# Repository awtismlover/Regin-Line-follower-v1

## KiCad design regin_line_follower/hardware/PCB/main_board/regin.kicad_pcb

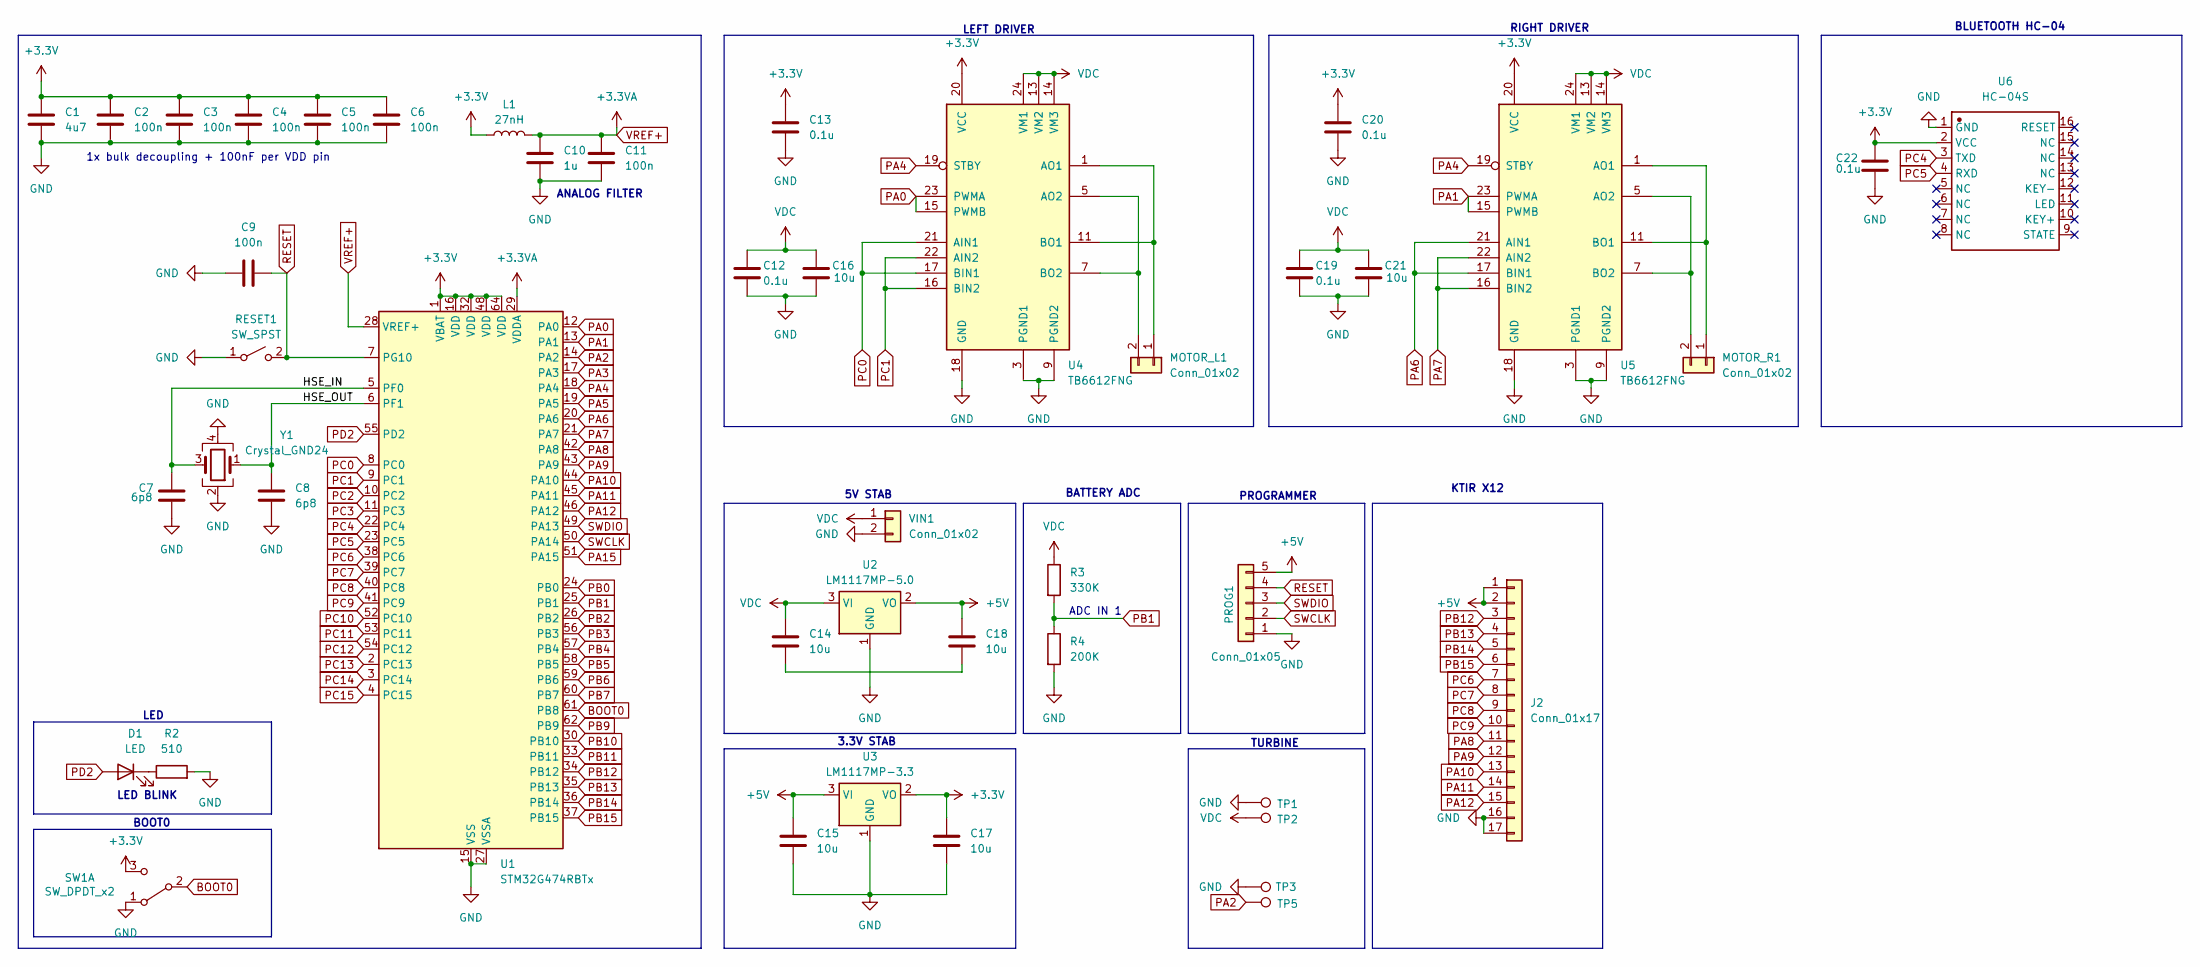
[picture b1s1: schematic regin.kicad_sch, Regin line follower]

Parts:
C1: 4u7; C_0603_1608Metric
C2, C3, C4, C5, C6, C9, C11: 100n; C_0603_1608Metric
C7, C8: 6p8; C_0603_1608Metric
C10: 1u; C_0603_1608Metric
C12, C13, C19, C20, C22: 0.1u; C_0603_1608Metric
C14, C15, C16, C17, C18, C21: 10u; C_0603_1608Metric
D1: LED; LED_0603_1608Metric
J2: Conn_01x17; Hirose_FH12-17S-0.5SH_1x17-1MP_P0.50mm_Horizontal
L1: 27nH; L_0603_1608Metric
MOTOR_L1: Conn_01x02; PinHeader_1x02_P2.54mm_Vertical
MOTOR_R1: Conn_01x02; PinHeader_1x02_P2.54mm_Vertical
PROG1: Conn_01x05; PinHeader_1x05_P2.54mm_Vertical
R2: 510; C_0603_1608Metric
R3: 330K; C_0603_1608Metric
R4: 200K; C_0603_1608Metric
RESET1: SW_SPST; SW_SPST_CK_RS282G05A3
SW1: SW_DPDT_x2; SW_SPDT_PCM12
TP1, TP2: TestPoint; TestPoint_Pad_D2.5mm
TP3, TP5: TestPoint; TestPoint_Pad_D1.0mm
U1: STM32G474RBTx; LQFP-64_10x10mm_P0.5mm
U2: LM1117MP-5.0; SOT-223-3_TabPin2
U3: LM1117MP-3.3; SOT-223-3_TabPin2
U4, U5: TB6612FNG; SSOP-24_5.3x8.2mm_P0.65mm
U6: HC-04S; hc-04; Manufacturer Part HC-04S
VIN1: Conn_01x02; PinSocket_1x02_P2.54mm_Vertical
Y1: Crystal_GND24; Crystal_SMD_2016-4Pin_2.0x1.6mm

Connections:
+3.3V: C1.1, C2.1, C3.1, C4.1, C5.1, C6.1, C13.1, C17.1, C20.1, C22.2, L1.1, SW1.3 (C), U1.1 (VBAT), U1.16 (VDD), U1.32 (VDD), U1.48 (VDD), U1.64 (VDD), U3.2 (VO), U4.20 (VCC), U5.20 (VCC), U6.2 (VCC)
+5V: C15.1, C18.1, J2.1, J2.2, PROG1.5, U2.2 (VO), U3.3 (VI)
/HSE_IN: C7.1, U1.5 (PF0), Y1.3
/HSE_OUT: C8.1, U1.6 (PF1), Y1.1
BOOT0: SW1.2 (B), U1.61 (PB8)
GND: C1.2, C2.2, C3.2, C4.2, C5.2, C6.2, C7.2, C8.2, C9.1, C10.2, C11.2, C12.2, C13.2, C15.2, C16.2, C17.2, C19.2, C20.2, C21.2, C22.1, J2.16, J2.17, PROG1.1, R2.2, R4.2, RESET1.1 (A), SW1.1 (A), TP1.1, TP3.1, U1.15 (VSS), U1.27 (VSSA), U1.31 (VSS), U1.47 (VSS), U1.63 (VSS), U2.1 (GND), U3.1 (GND), U4.3 (PGND1), U4.4 (PGND1), U4.9 (PGND2), U4.10 (PGND2), U4.18 (GND), U5.3 (PGND1), U5.4 (PGND1), U5.9 (PGND2), U5.10 (PGND2), U5.18 (GND), U6.1 (GND), VIN1.2, Y1.2, Y1.4; also elsewhere on the board
unnamed: C14.2, C18.2
unnamed: D1.1 (K), R2.1
unnamed: MOTOR_L1.1, U4.1 (AO1), U4.2 (AO1), U4.11 (BO1), U4.12 (BO1)
unnamed: MOTOR_L1.2, U4.5 (AO2), U4.6 (AO2), U4.7 (BO2), U4.8 (BO2)
unnamed: MOTOR_R1.1, U5.1 (AO1), U5.2 (AO1), U5.11 (BO1), U5.12 (BO1)
unnamed: MOTOR_R1.2, U5.5 (AO2), U5.6 (AO2), U5.7 (BO2), U5.8 (BO2)
PA0: U1.12 (PA0), U4.15 (PWMB), U4.23 (PWMA)
PA1: U1.13 (PA1), U5.15 (PWMB), U5.23 (PWMA)
PA2: TP5.1, U1.14 (PA2); also elsewhere on the board
PA3: U1.17 (PA3)
PA4: U1.18 (PA4), U4.19 (STBY), U5.19 (STBY)
PA5: U1.19 (PA5)
PA6: U1.20 (PA6), U5.17 (BIN1), U5.21 (AIN1)
PA7: U1.21 (PA7), U5.16 (BIN2), U5.22 (AIN2)
PA8: J2.11, U1.42 (PA8)
PA9: J2.12, U1.43 (PA9)
PA10: J2.13, U1.44 (PA10)
PA11: J2.14, U1.45 (PA11)
PA12: J2.15, U1.46 (PA12)
PA15: U1.51 (PA15)
PB0: U1.24 (PB0)
PB1: R3.2, R4.1, U1.25 (PB1)
PB2: U1.26 (PB2)
PB3: U1.56 (PB3)
PB4: U1.57 (PB4)
PB5: U1.58 (PB5)
PB6: U1.59 (PB6)
PB7: U1.60 (PB7)
PB9: U1.62 (PB9)
PB10: U1.30 (PB10)
PB11: U1.33 (PB11)
PB12: J2.3, U1.34 (PB12)
PB13: J2.4, U1.35 (PB13)
PB14: J2.5, U1.36 (PB14)
PB15: J2.6, U1.37 (PB15)
PC0: U1.8 (PC0), U4.17 (BIN1), U4.21 (AIN1)
PC1: U1.9 (PC1), U4.16 (BIN2), U4.22 (AIN2)
PC2: U1.10 (PC2)
PC3: U1.11 (PC3)
PC4: U1.22 (PC4), U6.3 (TXD)
PC5: U1.23 (PC5), U6.4 (RXD)
PC6: J2.7, U1.38 (PC6)
PC7: J2.8, U1.39 (PC7)
PC8: J2.9, U1.40 (PC8)
PC9: J2.10, U1.41 (PC9)
PC10: U1.52 (PC10)
PC11: U1.53 (PC11)
PC12: U1.54 (PC12)
PC13: U1.2 (PC13)
PC14: U1.3 (PC14)
PC15: U1.4 (PC15)
PD2: D1.2 (A), U1.55 (PD2)
RESET: C9.2, PROG1.4, RESET1.2 (B), U1.7 (PG10)
SWCLK: PROG1.2, U1.50 (PA14)
SWDIO: PROG1.3, U1.49 (PA13)
VDC: C12.1, C14.1, C16.1, C19.1, C21.1, R3.1, TP2.1, U2.3 (VI), U4.13 (VM2), U4.14 (VM3), U4.24 (VM1), U5.13 (VM2), U5.14 (VM3), U5.24 (VM1), VIN1.1; also elsewhere on the board
VREF+: C10.1, C11.1, L1.2, U1.28 (VREF+), U1.29 (VDDA)

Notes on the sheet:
ADC IN 1
ANALOG FILTER
TURBINE
1x bulk decoupling + 100nF per VDD pin
RIGHT DRIVER
3.3V STAB
LED
BATTERY ADC
5V STAB
BLUETOOTH HC-04
PROGRAMMER
KTIR X12
BOOT0
LEFT DRIVER
LED BLINK

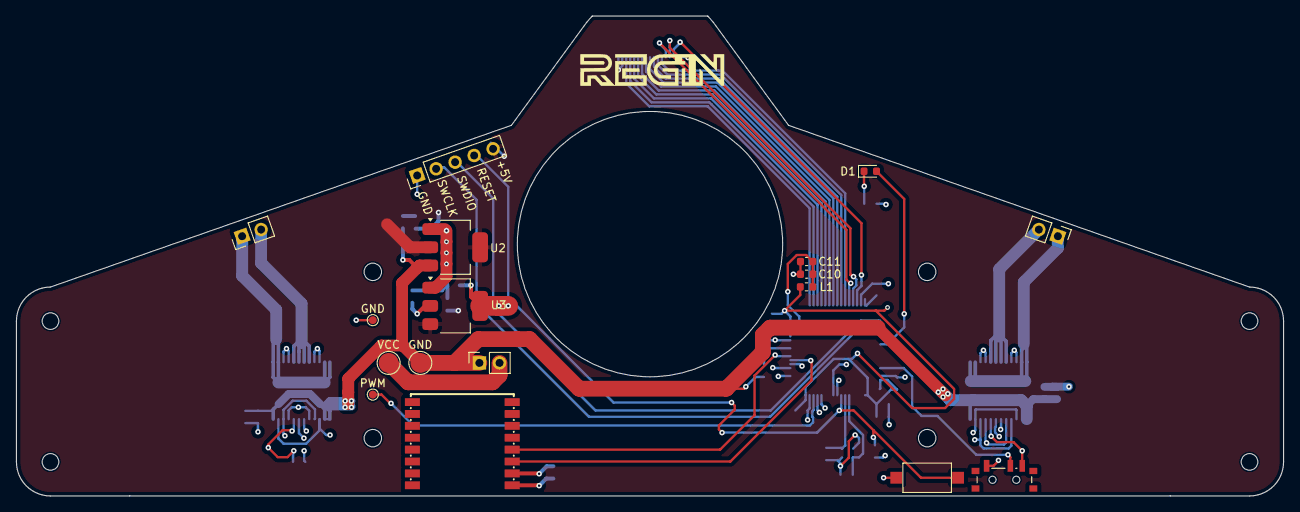
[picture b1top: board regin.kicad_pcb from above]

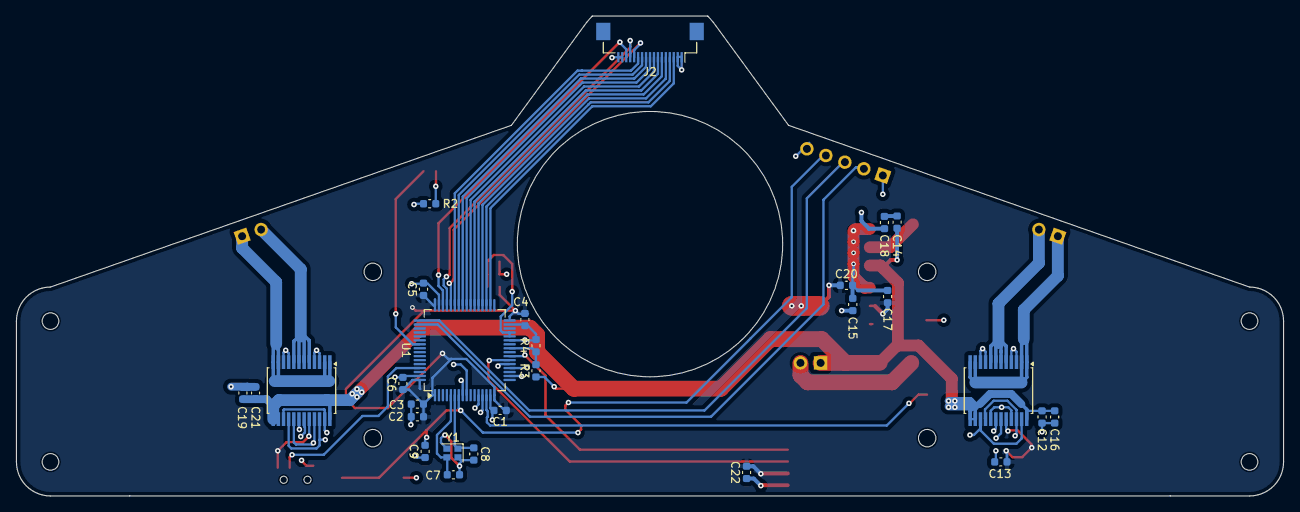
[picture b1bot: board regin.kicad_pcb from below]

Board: 4 copper layers, 160.0 x 60.6 mm, 49 parts (28 on the bottom side), 42 nets.

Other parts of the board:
GND: TestPoint; TestPoint_Pad_D2.5mm
GND#2: TestPoint; TestPoint_Pad_D1.0mm
H1, H2, H3, H4: MountingHole; MountingHole_2.2mm_M2
PWM: TestPoint; TestPoint_Pad_D1.0mm
VCC: TestPoint; TestPoint_Pad_D2.5mm

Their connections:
GND: GND#2.1, VCC.1; also elsewhere on the board
PA2: PWM.1; also elsewhere on the board
VDC: GND.1; also elsewhere on the board

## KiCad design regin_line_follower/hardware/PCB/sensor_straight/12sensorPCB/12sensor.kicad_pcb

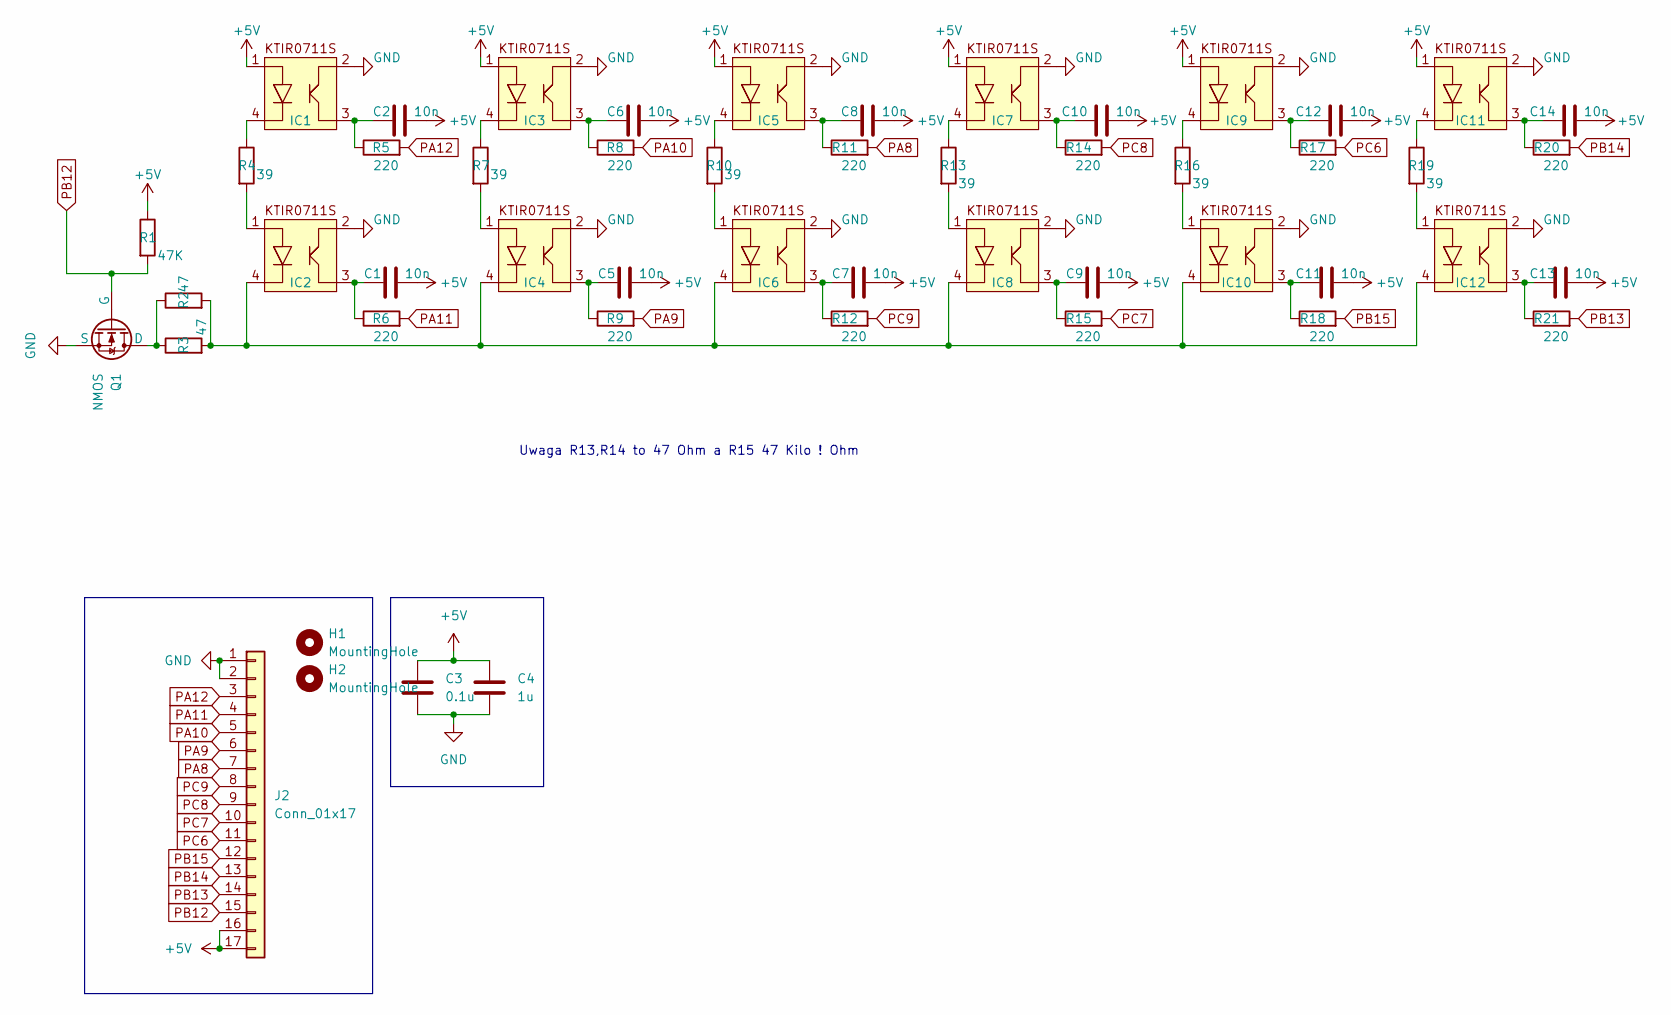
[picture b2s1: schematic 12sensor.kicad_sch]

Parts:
C1, C2, C5, C6, C7, C8, C9, C10, C11, C12, C13, C14: 10n; C_0603_1608Metric
C3: 0.1u; C_0603_1608Metric
C4: 1u; C_0603_1608Metric
H1, H2: MountingHole; MountingHole_2.2mm_M2
IC1, IC2, IC3, IC4, IC5, IC6, IC7, IC8, IC9, IC10, IC11, IC12: KTIR0711S
J2: Conn_01x17; Hirose_FH12-17S-0.5SH_1x17-1MP_P0.50mm_Horizontal
Q1: NMOS; NMOS_SN
R1: 47K; R_0603_1608Metric
R2, R3: 47; R_0603_1608Metric
R4, R7, R10, R13, R16, R19: 39; R_0603_1608Metric
R5, R6, R8, R9, R11, R12, R14, R15, R17, R18, R20, R21: 220; R_0603_1608Metric

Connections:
+5V: C1.2, C2.2, C3.1, C4.1, C5.2, C6.2, C7.2, C8.2, C9.2, C10.2, C11.2, C12.2, C13.2, C14.2, IC1.1, IC3.1, IC5.1, IC7.1, IC9.1, IC11.1, J2.16, J2.17, R1.1; also elsewhere on the board
GND: C3.2, C4.2, IC1.2, IC2.2, IC3.2, IC4.2, IC5.2, IC6.2, IC7.2, IC8.2, IC9.2, IC10.2, IC11.2, IC12.2, J2.1, J2.2, Q1.3 (S); also elsewhere on the board
unnamed: C1.1, IC2.3, R6.1
unnamed: C2.1, IC1.3, R5.1
unnamed: C5.1, IC4.3, R9.1
unnamed: C6.1, IC3.3, R8.1
unnamed: C7.1, IC6.3, R12.1
unnamed: C8.1, IC5.3, R11.1
unnamed: C9.1, IC8.3, R15.1
unnamed: C10.1, IC7.3, R14.1
unnamed: C11.1, IC10.3, R18.1
unnamed: C12.1, IC9.3, R17.1
unnamed: C13.1, IC12.3, R21.1
unnamed: C14.1, IC11.3, R20.1
unnamed: IC1.4, R4.1
unnamed: IC2.1, R4.2
unnamed: IC3.4, R7.1
unnamed: IC4.1, R7.2
unnamed: IC5.4, R10.1
unnamed: IC6.1, R10.2
unnamed: IC7.4, R13.1
unnamed: IC8.1, R13.2
unnamed: IC9.4, R16.1
unnamed: IC10.1, R16.2
unnamed: IC2.4, IC4.4, IC6.4, IC8.4, IC10.4, IC12.4, R2.2, R3.2
unnamed: IC11.4, R19.1
unnamed: IC12.1, R19.2
unnamed: Q1.1 (D), R2.1, R3.1
PA8: J2.7, R11.2; also elsewhere on the board
PA9: J2.6, R9.2; also elsewhere on the board
PA10: J2.5, R8.2; also elsewhere on the board
PA11: J2.4, R6.2; also elsewhere on the board
PA12: J2.3, R5.2; also elsewhere on the board
PB12: J2.15, Q1.2 (G), R1.2; also elsewhere on the board
PB13: J2.14, R21.2; also elsewhere on the board
PB14: J2.13, R20.2; also elsewhere on the board
PB15: J2.12, R18.2; also elsewhere on the board
PC6: J2.11, R17.2; also elsewhere on the board
PC7: J2.10, R15.2; also elsewhere on the board
PC8: J2.9, R14.2; also elsewhere on the board
PC9: J2.8, R12.2; also elsewhere on the board

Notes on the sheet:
Uwaga R13,R14 to 47 Ohm a R15 47 Kilo ! Ohm

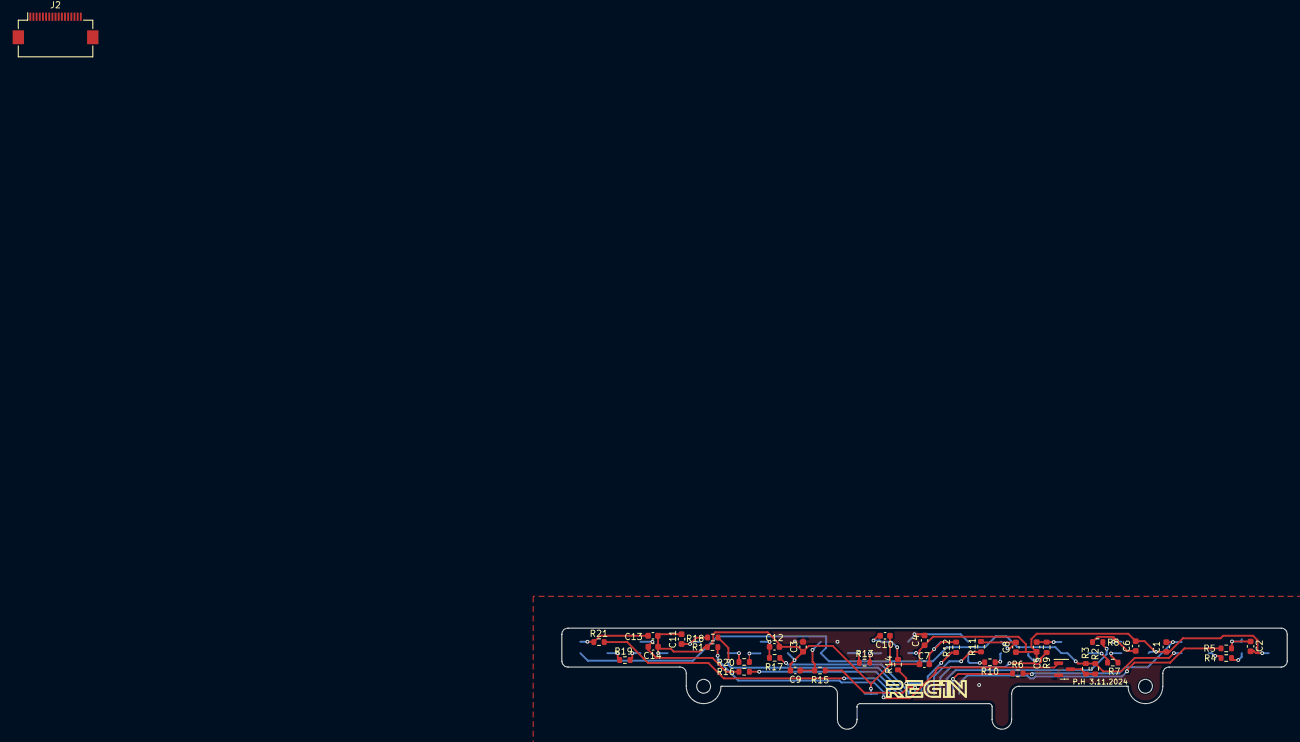
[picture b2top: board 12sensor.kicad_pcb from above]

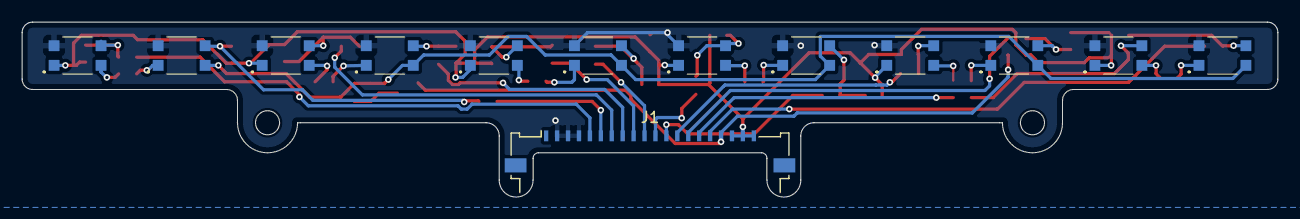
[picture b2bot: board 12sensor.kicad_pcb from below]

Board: 2 copper layers, 114.9 x 16.0 mm, 52 parts (13 on the bottom side), 41 nets.

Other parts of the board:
J1: Conn_01x20; Molex_200528-0200_1x20-1MP_P1.00mm_Horizontal

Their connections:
+5V: J1.18, J1.19, J1.20; also elsewhere on the board
GND: J1.2, J1.3, J1.4; also elsewhere on the board
PA8: J1.9; also elsewhere on the board
PA9: J1.8; also elsewhere on the board
PA10: J1.7; also elsewhere on the board
PA11: J1.6; also elsewhere on the board
PA12: J1.5; also elsewhere on the board
PB12: J1.17; also elsewhere on the board
PB13: J1.16; also elsewhere on the board
PB14: J1.15; also elsewhere on the board
PB15: J1.14; also elsewhere on the board
PC6: J1.13; also elsewhere on the board
PC7: J1.12; also elsewhere on the board
PC8: J1.11; also elsewhere on the board
PC9: J1.10; also elsewhere on the board

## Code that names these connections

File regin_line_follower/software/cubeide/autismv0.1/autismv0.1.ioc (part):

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Mcu.Name=STM32G474R(B-C-E)Tx
Mcu.Package=LQFP64
Mcu.UserName=STM32G474RETx
PA0.Signal=S_TIM2_CH1
PA1.Signal=S_TIM2_CH2
PA10.GPIOParameters=GPIO_Label
PA10.GPIO_Label=SENSOR3
PA10.Signal=GPIO_Output
PA11.GPIOParameters=GPIO_Label
PA11.GPIO_Label=SENSOR2
PA11.Signal=GPIO_Output
PA12.GPIOParameters=GPIO_Label
PA12.GPIO_Label=SENSOR1
PA12.Signal=GPIO_Output
PA13.Mode=Serial_Wire
PA13.Signal=SYS_JTMS-SWDIO
PA14.Mode=Serial_Wire
PA14.Signal=SYS_JTCK-SWCLK
PA2.Signal=S_TIM2_CH3
PA4.GPIOParameters=GPIO_Label
PA4.GPIO_Label=STNDBY
PA4.Signal=GPIO_Output
PA6.GPIOParameters=GPIO_Label
PA6.GPIO_Label=IN_1R
PA6.Signal=GPIO_Output
PA7.GPIOParameters=GPIO_Label
PA7.GPIO_Label=IN_2R
PA7.Signal=GPIO_Output
PA8.GPIOParameters=GPIO_Label
PA8.GPIO_Label=SENSOR5
PA8.Signal=GPIO_Output
PA9.GPIOParameters=GPIO_Label
PA9.GPIO_Label=SENSOR4
PA9.Signal=GPIO_Output
PB1.Mode=IN1-Single-Ended
PB1.Signal=ADC3_IN1
PB10.Mode=Asynchronous
PB10.Signal=USART3_TX
PB11.Mode=Asynchronous
PB11.Signal=USART3_RX
PB12.GPIOParameters=GPIO_Label
PB12.GPIO_Label=LEDON
PB12.Signal=GPIO_Output
PB13.GPIOParameters=GPIO_Label
PB13.GPIO_Label=SENSOR12
PB13.Signal=GPIO_Output
PB14.GPIOParameters=GPIO_Label
PB14.GPIO_Label=SENSOR11
PB14.Signal=GPIO_Output
PB15.GPIOParameters=GPIO_Label
PB15.GPIO_Label=SENSOR10
PB15.Signal=GPIO_Output
PC0.GPIOParameters=GPIO_Label
PC0.GPIO_Label=IN_1L
PC0.Signal=GPIO_Input
PC1.GPIOParameters=GPIO_Label
PC1.GPIO_Label=IN_2L
PC1.Signal=GPIO_Input
PC6.GPIOParameters=GPIO_Label
PC6.GPIO_Label=SENSOR9
PC6.Signal=GPIO_Output
PC7.GPIOParameters=GPIO_Label
PC7.GPIO_Label=SENSOR8
PC7.Signal=GPIO_Output
PC8.GPIOParameters=GPIO_Label
PC8.GPIO_Label=SENSOR7
PC8.Signal=GPIO_Output
PC9.GPIOParameters=GPIO_Label
PC9.GPIO_Label=SENSOR6
PC9.Signal=GPIO_Output
PD2.GPIOParameters=GPIO_Label
PD2.GPIO_Label=LD
PD2.Signal=GPIO_Output
PF0-OSC_IN.Mode=HSE-External-Oscillator
PF0-OSC_IN.Signal=RCC_OSC_IN
PF1-OSC_OUT.Mode=HSE-External-Oscillator
PF1-OSC_OUT.Signal=RCC_OSC_OUT
RCC.HSE_VALUE=8000000
RCC.SYSCLKFreq_VALUE=16000000
board=custom

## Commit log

2024-11-30 v1
    turbo
